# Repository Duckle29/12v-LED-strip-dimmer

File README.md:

# 12v-LED-strip-dimmer
A simple PWM based dimmer, using the ATTiny85 to dim a strip of LEDs

Runs on a 12v supply (Or whatever your choice of sot-223 regulator will do at 5v 20mA output)

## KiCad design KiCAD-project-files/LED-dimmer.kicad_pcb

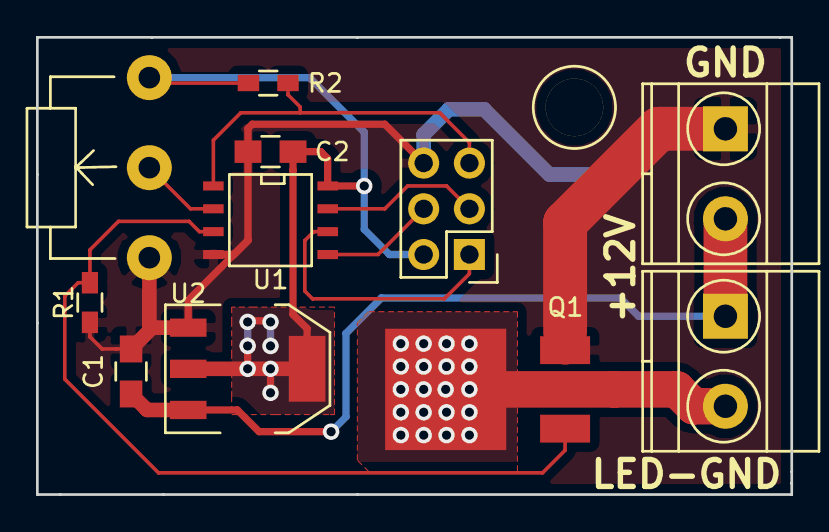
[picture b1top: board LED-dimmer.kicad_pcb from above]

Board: 2 copper layers, 41.9 x 25.4 mm, 11 parts (0 on the bottom side), 10 nets.

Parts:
C1, C2: C_Small; C_0805_HandSoldering
P1, P2: CONN_01X02; TerminalBlock_Pheonix_MKDS1.5-2pol
P3: CONN_02X03; Pin_Header_Straight_2x03
Q1: Q_NMOS_GDSD; D-Pak_TO252AA
R1, R2: 1k; R_0603_HandSoldering
RV1: POT; Potentiometer_WirePads
U1: ATTINY85-S; SOIC-8-N
U2: AP1117D50; SOT-223

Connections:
+5V: C2.1, P3.2, R2.2, RV1.3, U1.8, U2.2, U2.4
+12V: C1.1, P1.1, P2.2, U2.3
GND: C1.2, C2.2, P2.1, P3.6, Q1.3, R1.2, RV1.1, U1.4, U2.1
MISO: P3.1, U1.6
MOSI: P3.4, U1.5
unnamed: RV1.2, U1.2
unnamed: Q1.1, R1.1, U1.3
unnamed: P1.2, Q1.4
RST: P3.5, R2.1, U1.1
SCK: P3.3, U1.7

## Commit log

2015-12-19 Initual commit and push
2015-12-19 Added short description
2015-12-19 Added PDF
